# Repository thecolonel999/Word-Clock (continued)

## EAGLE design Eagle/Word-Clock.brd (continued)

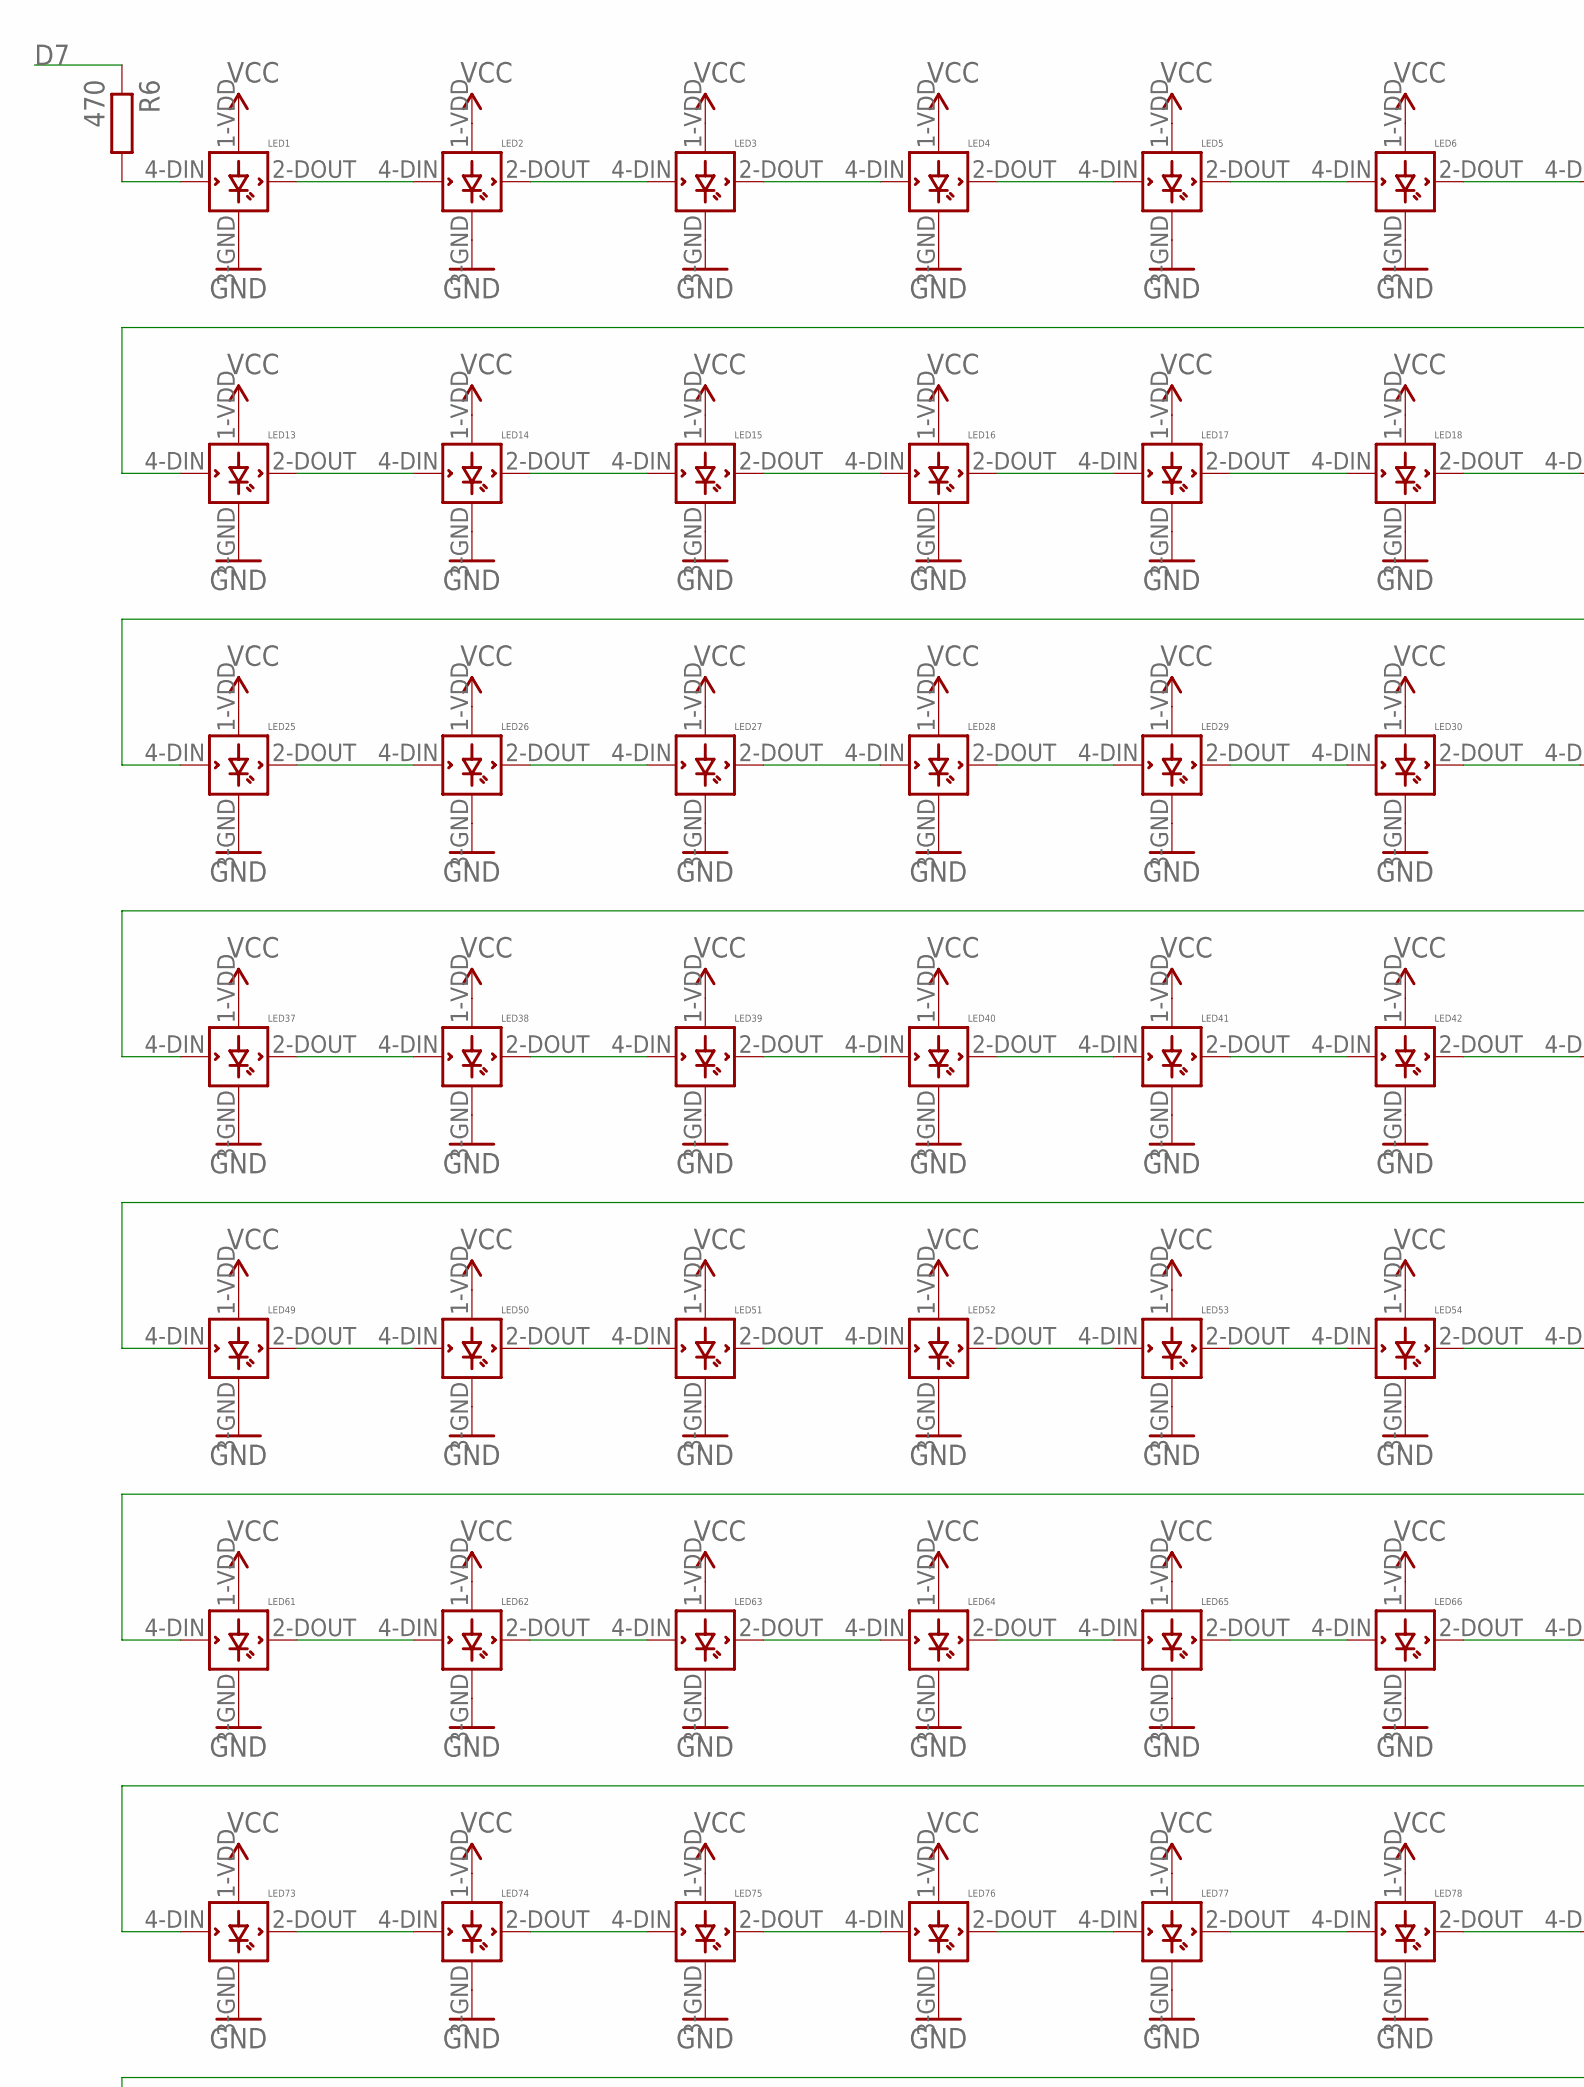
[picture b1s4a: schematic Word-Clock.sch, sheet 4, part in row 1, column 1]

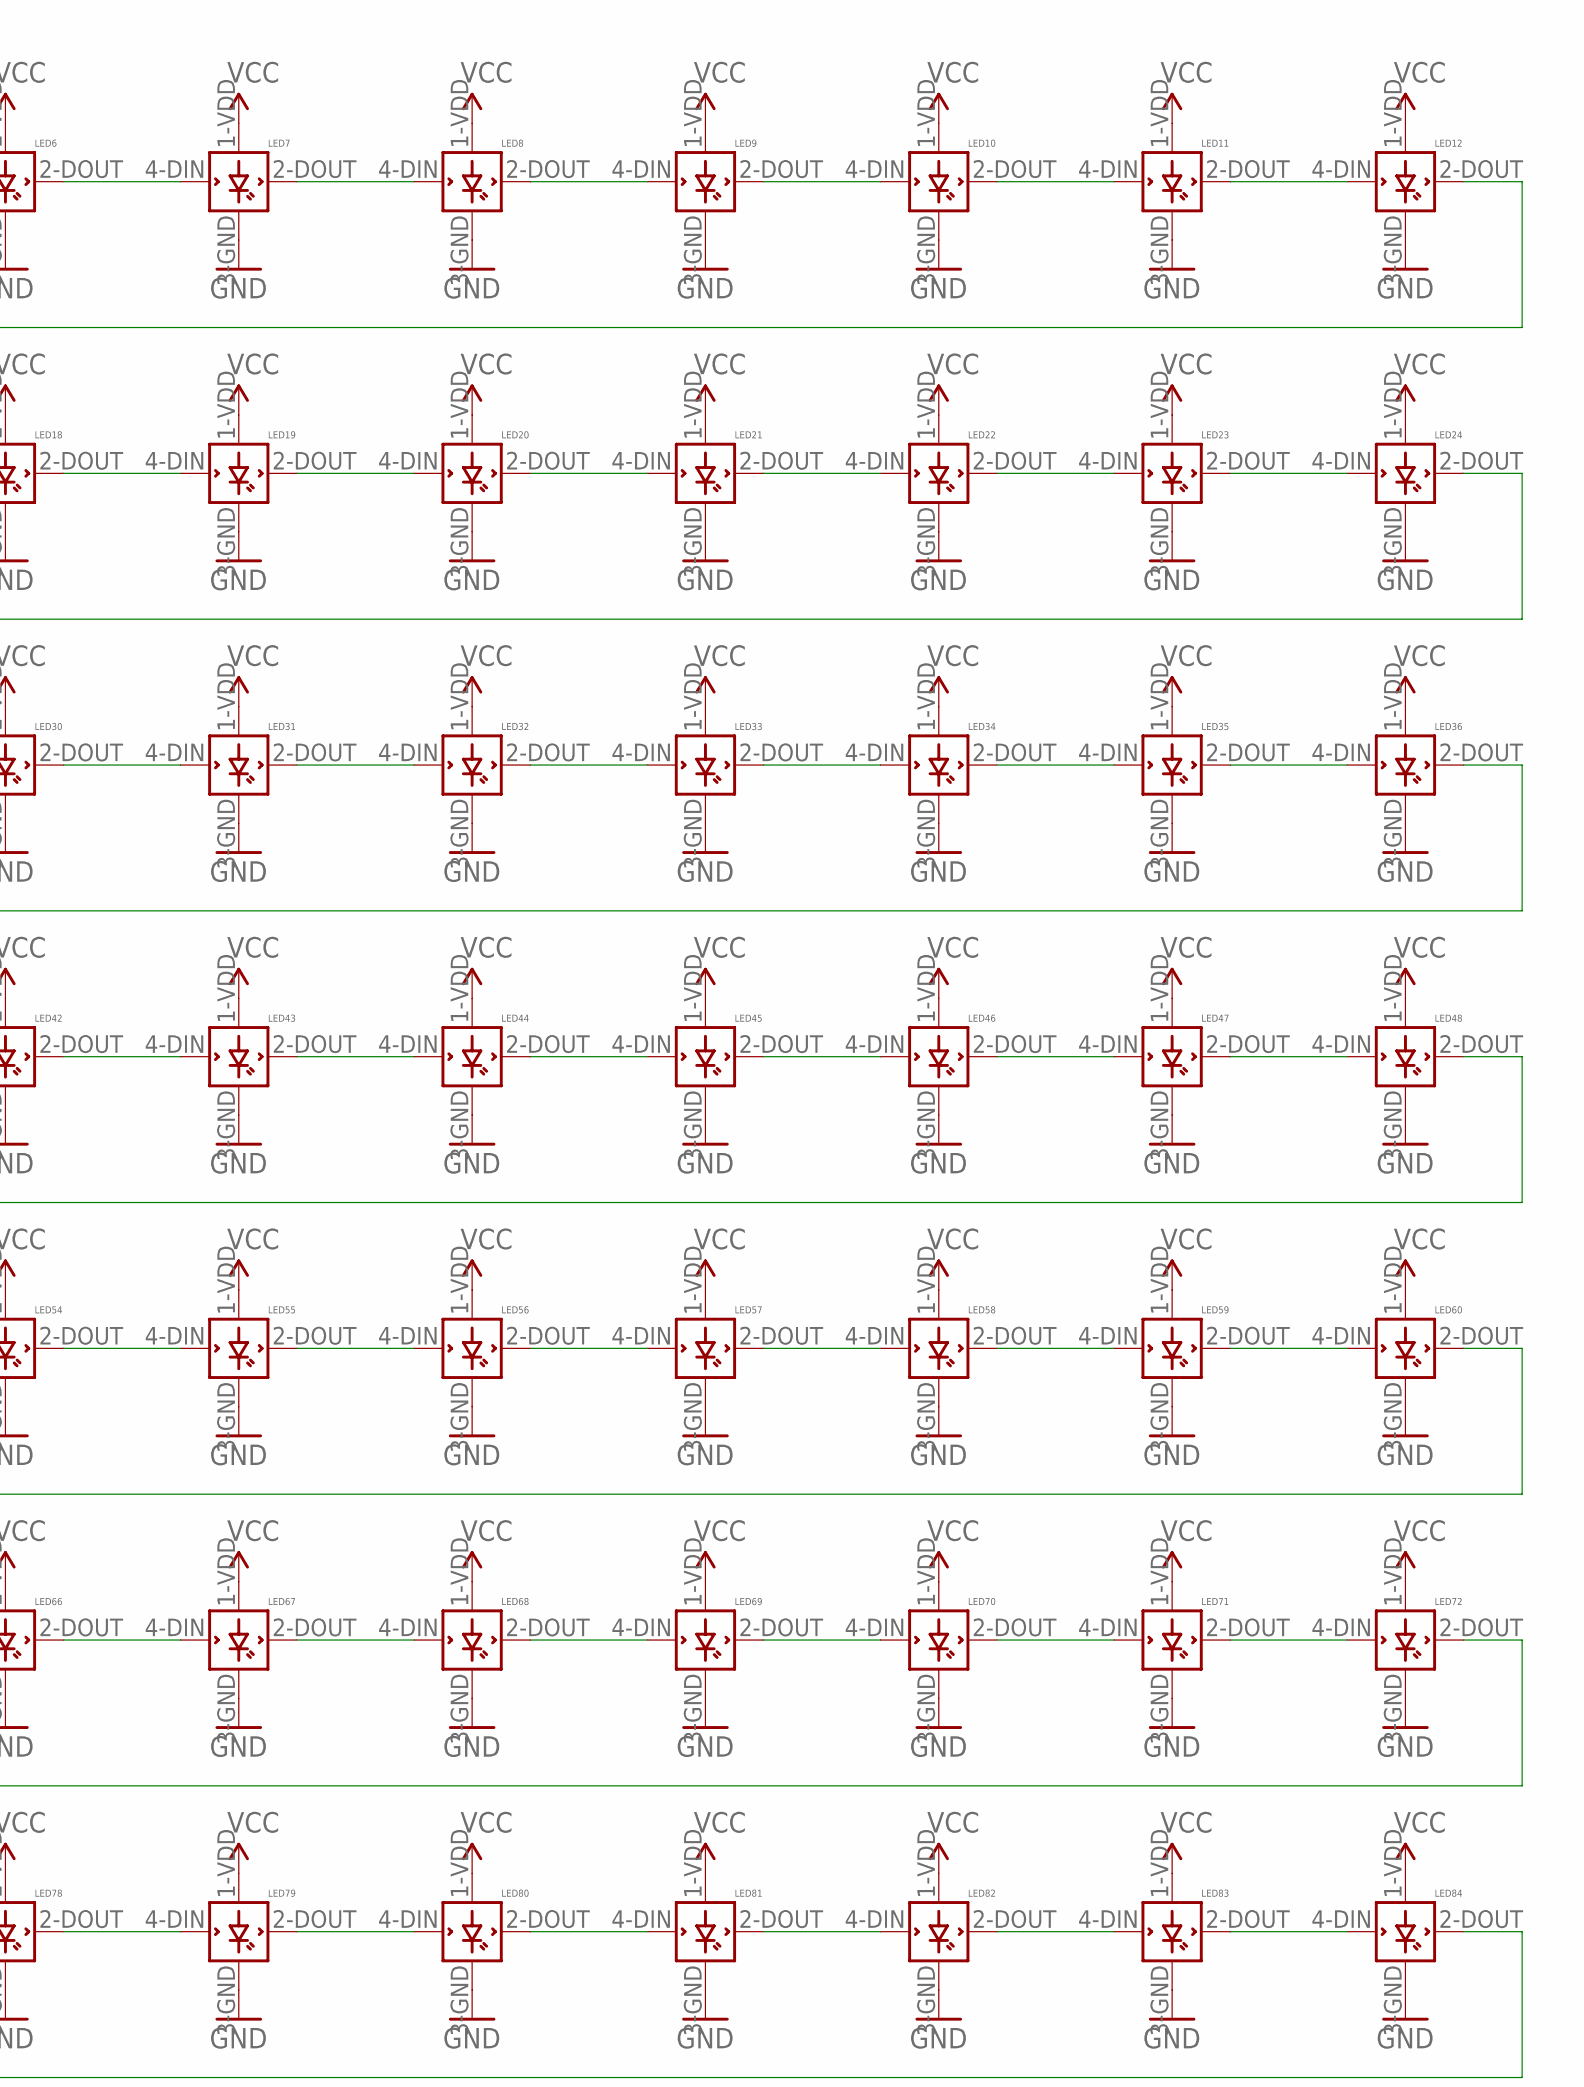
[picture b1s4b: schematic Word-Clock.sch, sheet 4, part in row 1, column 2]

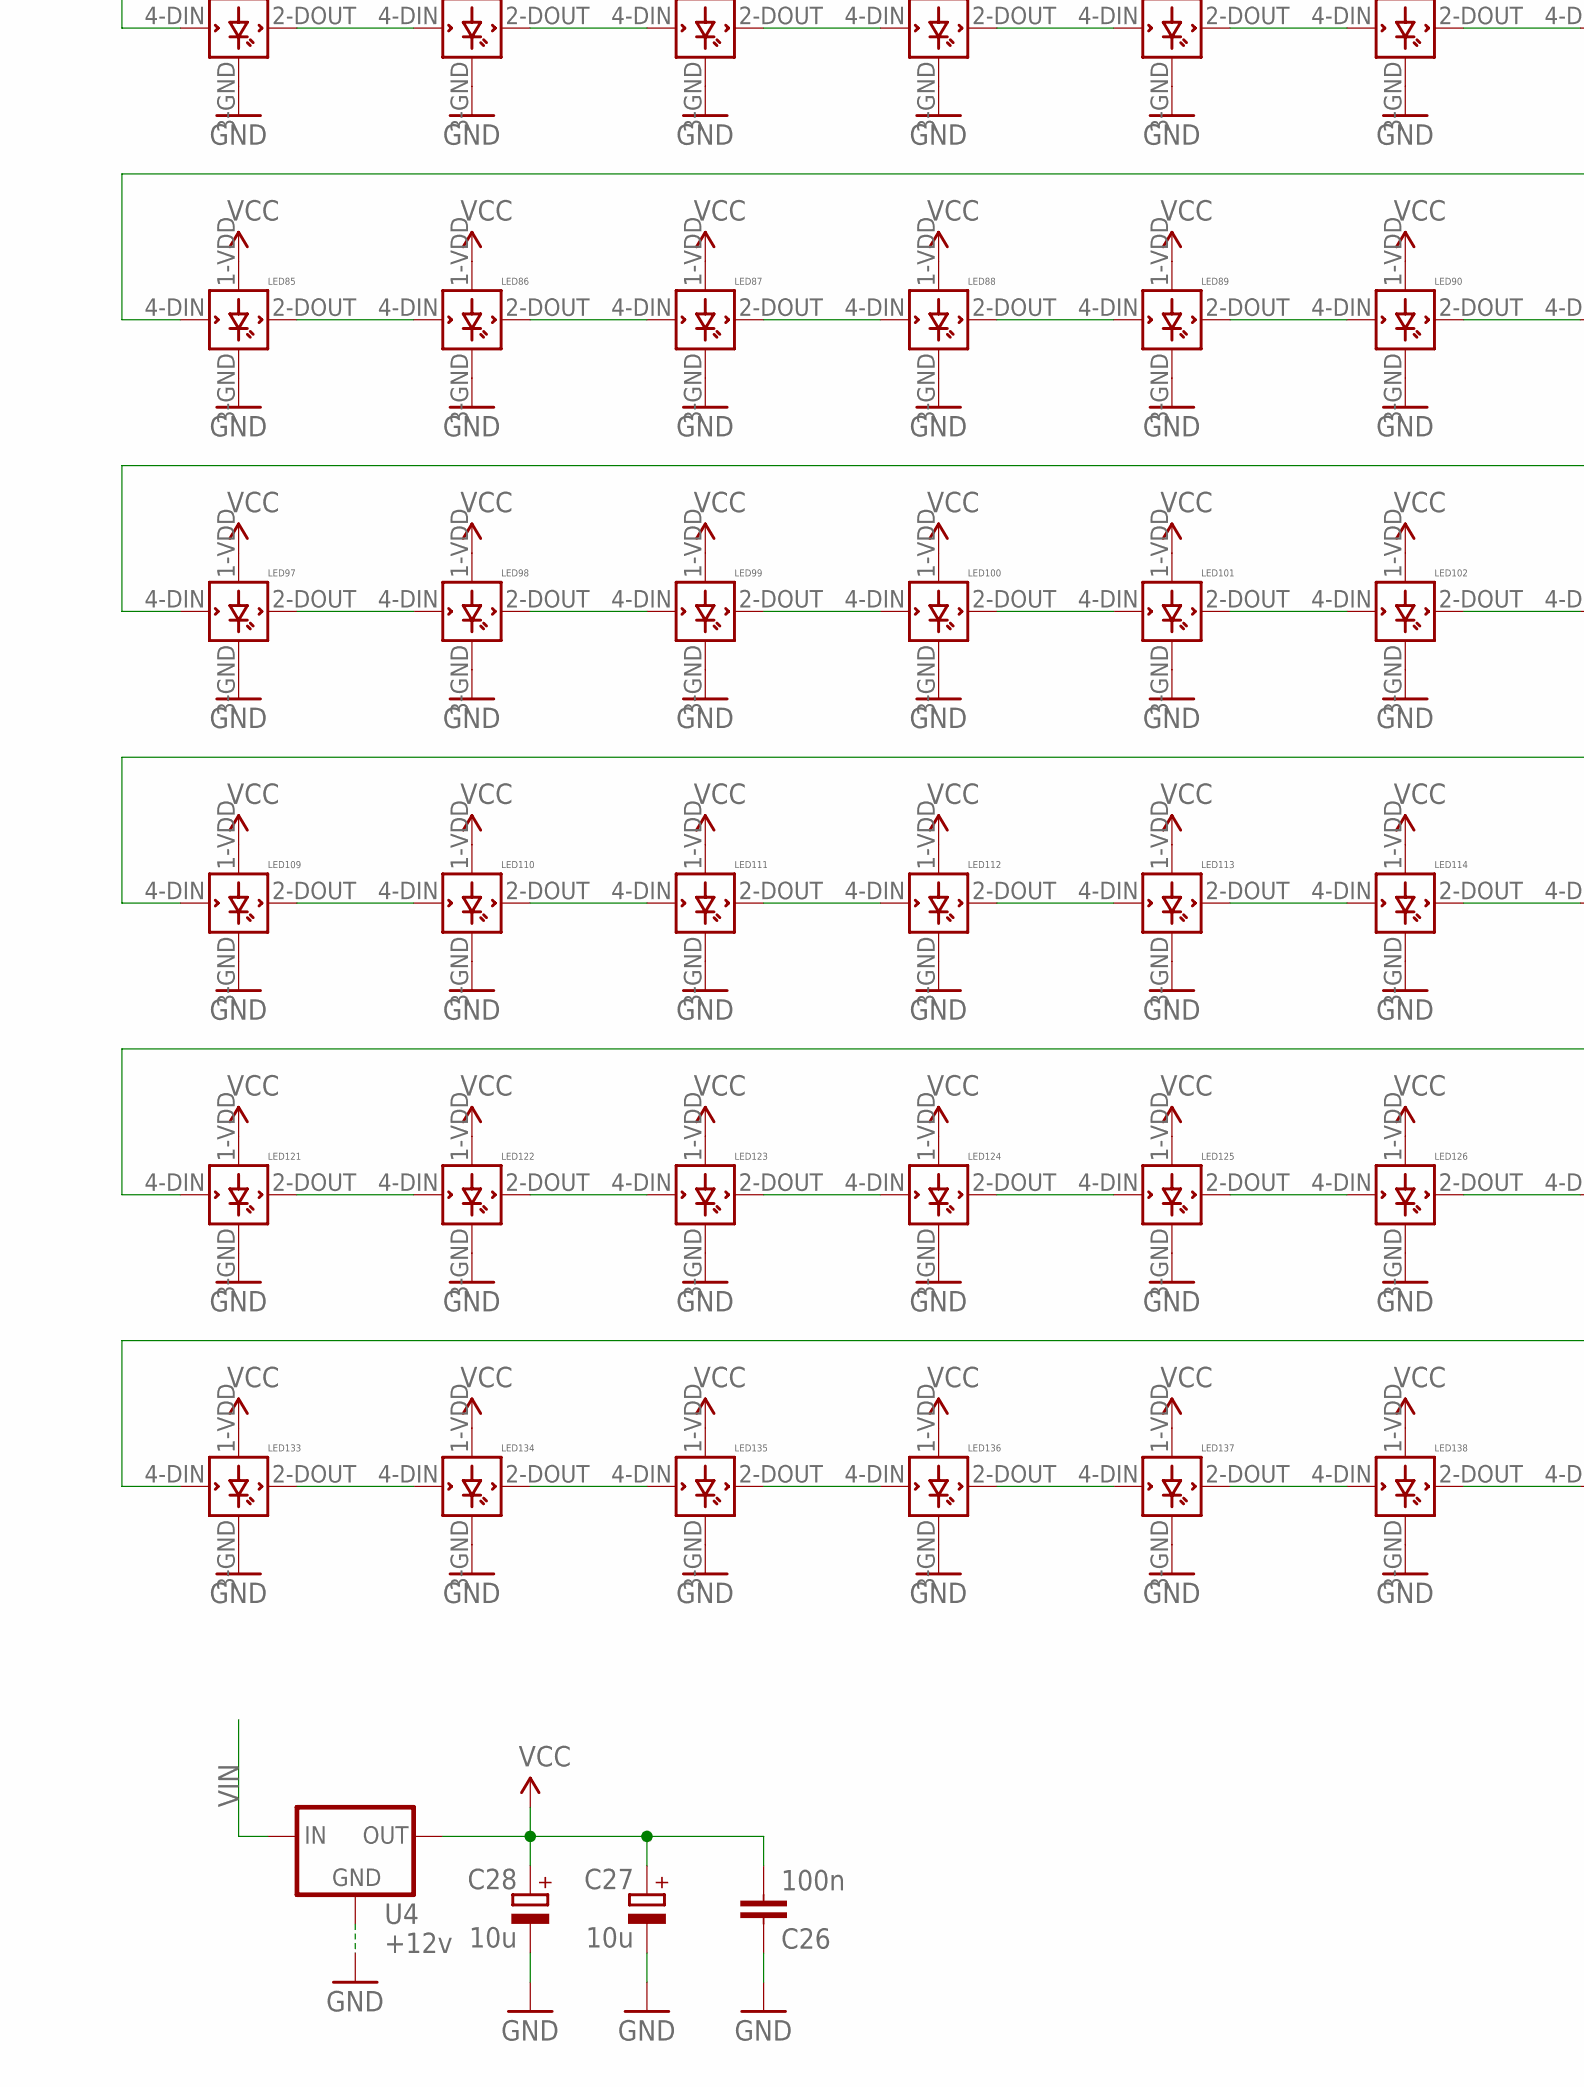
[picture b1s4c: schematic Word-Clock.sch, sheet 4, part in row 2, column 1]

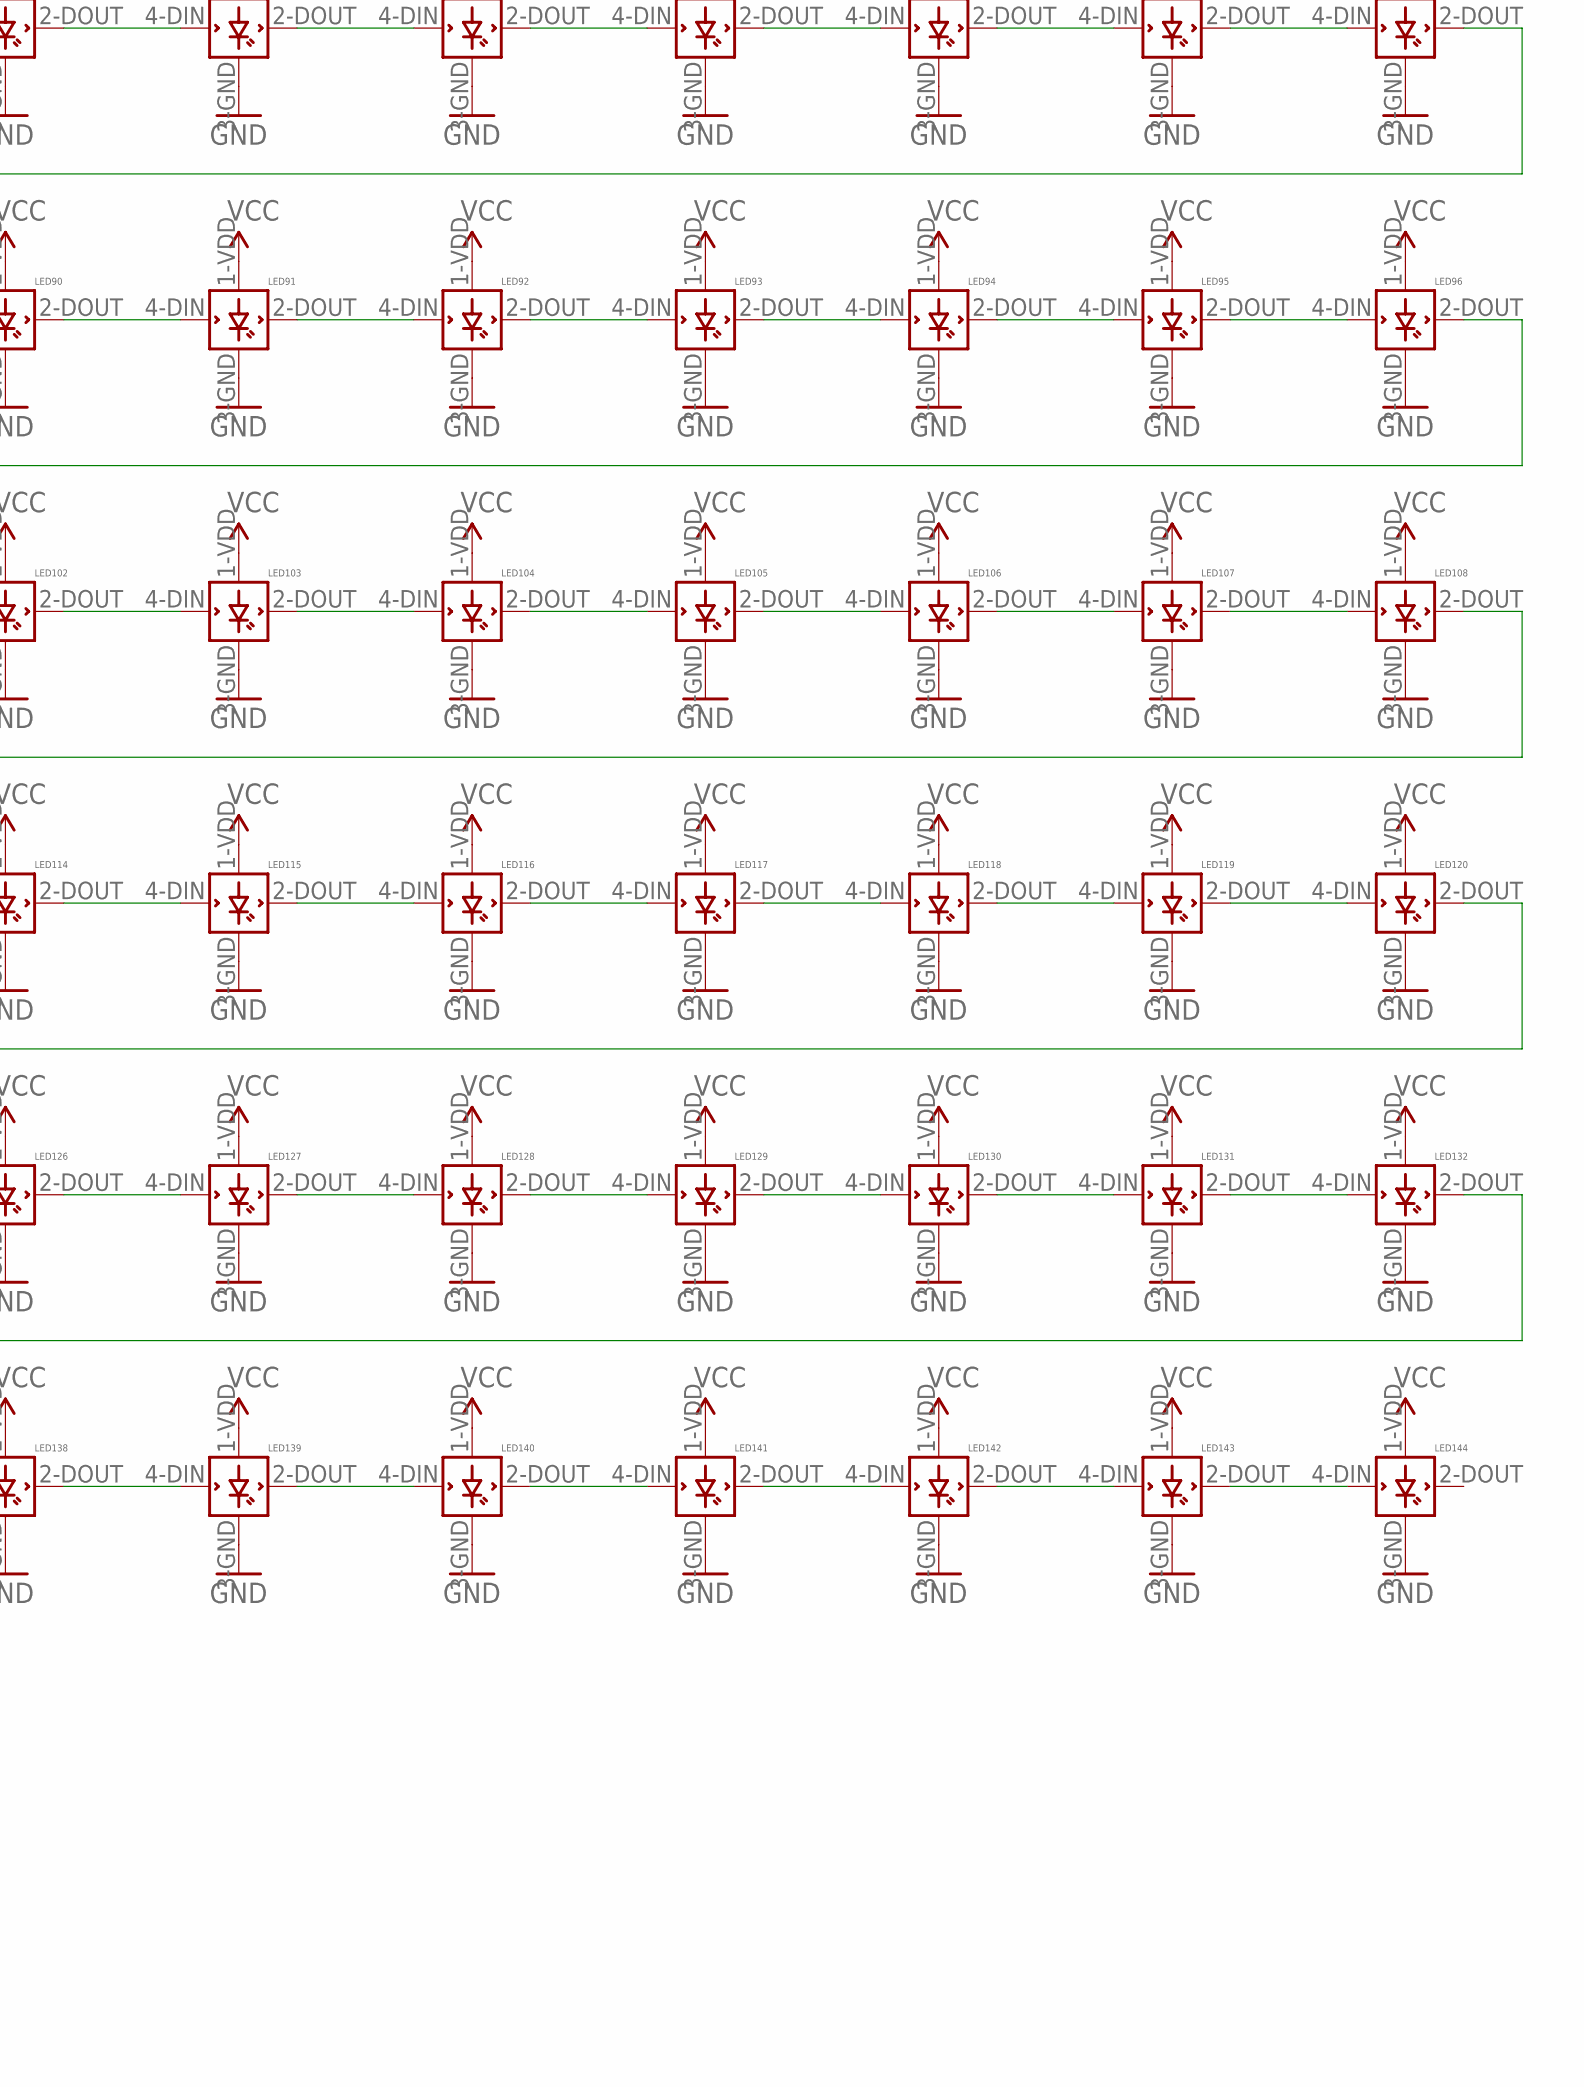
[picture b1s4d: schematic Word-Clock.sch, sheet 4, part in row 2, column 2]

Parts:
C26: 100n; C1206
C27, C28: 10u; B/3528-21W
LED1, LED2, LED3, LED4, LED5, LED6, LED7, LED8, LED9, LED10, LED11, LED12, LED13, LED14, LED15, LED16, LED17, LED18, LED19, LED20, LED21, LED22, LED23, LED24, LED25, LED26, LED27, LED28, LED29, LED30, LED31, LED32, LED33, LED34, LED35, LED36, LED37, LED38, LED39, LED40, LED41, LED42, LED43, LED44, LED45, LED46, LED47, LED48, LED49, LED50, LED51, LED52, LED53, LED54, LED55, LED56, LED57, LED58, LED59, LED60, LED61, LED62, LED63, LED64, LED65, LED66, LED67, LED68, LED69, LED70, LED71, LED72, LED73, LED74, LED75, LED76, LED77, LED78, LED79, LED80, LED81, LED82, LED83, LED84, LED85, LED86, LED87, LED88, LED89, LED90, LED91, LED92, LED93, LED94, LED95, LED96, LED97, LED98, LED99, LED100, LED101, LED102, LED103, LED104, LED105, LED106, LED107, LED108, LED109, LED110, LED111, LED112, LED113, LED114, LED115, LED116, LED117, LED118, LED119, LED120, LED121, LED122, LED123, LED124, LED125, LED126, LED127, LED128, LED129, LED130, LED131, LED132, LED133, LED134, LED135, LED136, LED137, LED138, LED139, LED140, LED141, LED142, LED143, LED144: WS2812B
R6: 470; R1206
U4: +12v; TO-252

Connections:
D7: R6.1; also elsewhere on the board
GND: C26.1, C27.-, C28.-, LED1.3-GND (GND), LED2.3-GND (GND), LED3.3-GND (GND), LED4.3-GND (GND), LED5.3-GND (GND), LED6.3-GND (GND), LED7.3-GND (GND), LED8.3-GND (GND), LED9.3-GND (GND), LED10.3-GND (GND), LED11.3-GND (GND), LED12.3-GND (GND), LED13.3-GND (GND), LED14.3-GND (GND), LED15.3-GND (GND), LED16.3-GND (GND), LED17.3-GND (GND), LED18.3-GND (GND), LED19.3-GND (GND), LED20.3-GND (GND), LED21.3-GND (GND), LED22.3-GND (GND), LED23.3-GND (GND), LED24.3-GND (GND), LED25.3-GND (GND), LED26.3-GND (GND), LED27.3-GND (GND), LED28.3-GND (GND), LED29.3-GND (GND), LED30.3-GND (GND), LED31.3-GND (GND), LED32.3-GND (GND), LED33.3-GND (GND), LED34.3-GND (GND), LED35.3-GND (GND), LED36.3-GND (GND), LED37.3-GND (GND), LED38.3-GND (GND), LED39.3-GND (GND), LED40.3-GND (GND), LED41.3-GND (GND), LED42.3-GND (GND), LED43.3-GND (GND), LED44.3-GND (GND), LED45.3-GND (GND), LED46.3-GND (GND), LED47.3-GND (GND), LED48.3-GND (GND), LED49.3-GND (GND), LED50.3-GND (GND), LED51.3-GND (GND), LED52.3-GND (GND), LED53.3-GND (GND), LED54.3-GND (GND), LED55.3-GND (GND), LED56.3-GND (GND), LED57.3-GND (GND), LED58.3-GND (GND), LED59.3-GND (GND), LED60.3-GND (GND), LED61.3-GND (GND), LED62.3-GND (GND), LED63.3-GND (GND), LED64.3-GND (GND), LED65.3-GND (GND), LED66.3-GND (GND), LED67.3-GND (GND), LED68.3-GND (GND), LED69.3-GND (GND), LED70.3-GND (GND), LED71.3-GND (GND), LED72.3-GND (GND), LED73.3-GND (GND), LED74.3-GND (GND), LED75.3-GND (GND), LED76.3-GND (GND), LED77.3-GND (GND), LED78.3-GND (GND), LED79.3-GND (GND), LED80.3-GND (GND), LED81.3-GND (GND), LED82.3-GND (GND), LED83.3-GND (GND), LED84.3-GND (GND), LED85.3-GND (GND), LED86.3-GND (GND), LED87.3-GND (GND), LED88.3-GND (GND), LED89.3-GND (GND), LED90.3-GND (GND), LED91.3-GND (GND), LED92.3-GND (GND), LED93.3-GND (GND), LED94.3-GND (GND), LED95.3-GND (GND), LED96.3-GND (GND), LED97.3-GND (GND), LED98.3-GND (GND), LED99.3-GND (GND), LED100.3-GND (GND), LED101.3-GND (GND), LED102.3-GND (GND), LED103.3-GND (GND), LED104.3-GND (GND), LED105.3-GND (GND), LED106.3-GND (GND), LED107.3-GND (GND), LED108.3-GND (GND), LED109.3-GND (GND), LED110.3-GND (GND), LED111.3-GND (GND), LED112.3-GND (GND), LED113.3-GND (GND), LED114.3-GND (GND), LED115.3-GND (GND), LED116.3-GND (GND), LED117.3-GND (GND), LED118.3-GND (GND), LED119.3-GND (GND), LED120.3-GND (GND), LED121.3-GND (GND), LED122.3-GND (GND), LED123.3-GND (GND), LED124.3-GND (GND), LED125.3-GND (GND), LED126.3-GND (GND), LED127.3-GND (GND), LED128.3-GND (GND), LED129.3-GND (GND), LED130.3-GND (GND), LED131.3-GND (GND), LED132.3-GND (GND), LED133.3-GND (GND), LED134.3-GND (GND), LED135.3-GND (GND), LED136.3-GND (GND), LED137.3-GND (GND), LED138.3-GND (GND), LED139.3-GND (GND), LED140.3-GND (GND), LED141.3-GND (GND), LED142.3-GND (GND), LED143.3-GND (GND), LED144.3-GND (GND), U4.3 (GND); also elsewhere on the board
unnamed: LED1.2-DOUT (DOUT), LED2.4-DIN (DIN)
unnamed: LED2.2-DOUT (DOUT), LED3.4-DIN (DIN)
unnamed: LED3.2-DOUT (DOUT), LED4.4-DIN (DIN)
unnamed: LED4.2-DOUT (DOUT), LED5.4-DIN (DIN)
unnamed: LED5.2-DOUT (DOUT), LED6.4-DIN (DIN)
unnamed: LED6.2-DOUT (DOUT), LED7.4-DIN (DIN)
unnamed: LED7.2-DOUT (DOUT), LED8.4-DIN (DIN)
unnamed: LED8.2-DOUT (DOUT), LED9.4-DIN (DIN)
unnamed: LED9.2-DOUT (DOUT), LED10.4-DIN (DIN)
unnamed: LED10.2-DOUT (DOUT), LED11.4-DIN (DIN)
unnamed: LED11.2-DOUT (DOUT), LED12.4-DIN (DIN)
unnamed: LED13.2-DOUT (DOUT), LED14.4-DIN (DIN)
unnamed: LED14.2-DOUT (DOUT), LED15.4-DIN (DIN)
unnamed: LED15.2-DOUT (DOUT), LED16.4-DIN (DIN)
unnamed: LED16.2-DOUT (DOUT), LED17.4-DIN (DIN)
unnamed: LED17.2-DOUT (DOUT), LED18.4-DIN (DIN)
unnamed: LED18.2-DOUT (DOUT), LED19.4-DIN (DIN)
unnamed: LED19.2-DOUT (DOUT), LED20.4-DIN (DIN)
unnamed: LED20.2-DOUT (DOUT), LED21.4-DIN (DIN)
unnamed: LED21.2-DOUT (DOUT), LED22.4-DIN (DIN)
unnamed: LED22.2-DOUT (DOUT), LED23.4-DIN (DIN)
unnamed: LED23.2-DOUT (DOUT), LED24.4-DIN (DIN)
unnamed: LED25.2-DOUT (DOUT), LED26.4-DIN (DIN)
unnamed: LED26.2-DOUT (DOUT), LED27.4-DIN (DIN)
unnamed: LED27.2-DOUT (DOUT), LED28.4-DIN (DIN)
unnamed: LED28.2-DOUT (DOUT), LED29.4-DIN (DIN)
unnamed: LED29.2-DOUT (DOUT), LED30.4-DIN (DIN)
unnamed: LED30.2-DOUT (DOUT), LED31.4-DIN (DIN)
unnamed: LED31.2-DOUT (DOUT), LED32.4-DIN (DIN)
unnamed: LED32.2-DOUT (DOUT), LED33.4-DIN (DIN)
unnamed: LED33.2-DOUT (DOUT), LED34.4-DIN (DIN)
unnamed: LED34.2-DOUT (DOUT), LED35.4-DIN (DIN)
unnamed: LED35.2-DOUT (DOUT), LED36.4-DIN (DIN)
unnamed: LED37.2-DOUT (DOUT), LED38.4-DIN (DIN)
unnamed: LED38.2-DOUT (DOUT), LED39.4-DIN (DIN)
unnamed: LED39.2-DOUT (DOUT), LED40.4-DIN (DIN)
unnamed: LED40.2-DOUT (DOUT), LED41.4-DIN (DIN)
unnamed: LED41.2-DOUT (DOUT), LED42.4-DIN (DIN)
unnamed: LED42.2-DOUT (DOUT), LED43.4-DIN (DIN)
unnamed: LED43.2-DOUT (DOUT), LED44.4-DIN (DIN)
unnamed: LED44.2-DOUT (DOUT), LED45.4-DIN (DIN)
unnamed: LED45.2-DOUT (DOUT), LED46.4-DIN (DIN)
unnamed: LED46.2-DOUT (DOUT), LED47.4-DIN (DIN)
unnamed: LED47.2-DOUT (DOUT), LED48.4-DIN (DIN)
unnamed: LED49.2-DOUT (DOUT), LED50.4-DIN (DIN)
unnamed: LED50.2-DOUT (DOUT), LED51.4-DIN (DIN)
unnamed: LED51.2-DOUT (DOUT), LED52.4-DIN (DIN)
unnamed: LED52.2-DOUT (DOUT), LED53.4-DIN (DIN)
unnamed: LED53.2-DOUT (DOUT), LED54.4-DIN (DIN)
unnamed: LED54.2-DOUT (DOUT), LED55.4-DIN (DIN)
unnamed: LED55.2-DOUT (DOUT), LED56.4-DIN (DIN)
unnamed: LED56.2-DOUT (DOUT), LED57.4-DIN (DIN)
unnamed: LED57.2-DOUT (DOUT), LED58.4-DIN (DIN)
unnamed: LED58.2-DOUT (DOUT), LED59.4-DIN (DIN)
unnamed: LED59.2-DOUT (DOUT), LED60.4-DIN (DIN)
unnamed: LED61.2-DOUT (DOUT), LED62.4-DIN (DIN)
unnamed: LED62.2-DOUT (DOUT), LED63.4-DIN (DIN)
unnamed: LED63.2-DOUT (DOUT), LED64.4-DIN (DIN)
unnamed: LED64.2-DOUT (DOUT), LED65.4-DIN (DIN)
unnamed: LED65.2-DOUT (DOUT), LED66.4-DIN (DIN)
unnamed: LED66.2-DOUT (DOUT), LED67.4-DIN (DIN)
unnamed: LED67.2-DOUT (DOUT), LED68.4-DIN (DIN)
unnamed: LED68.2-DOUT (DOUT), LED69.4-DIN (DIN)
unnamed: LED69.2-DOUT (DOUT), LED70.4-DIN (DIN)
unnamed: LED70.2-DOUT (DOUT), LED71.4-DIN (DIN)
unnamed: LED71.2-DOUT (DOUT), LED72.4-DIN (DIN)
unnamed: LED73.2-DOUT (DOUT), LED74.4-DIN (DIN)
unnamed: LED74.2-DOUT (DOUT), LED75.4-DIN (DIN)
unnamed: LED75.2-DOUT (DOUT), LED76.4-DIN (DIN)
unnamed: LED76.2-DOUT (DOUT), LED77.4-DIN (DIN)
unnamed: LED77.2-DOUT (DOUT), LED78.4-DIN (DIN)
unnamed: LED78.2-DOUT (DOUT), LED79.4-DIN (DIN)
unnamed: LED79.2-DOUT (DOUT), LED80.4-DIN (DIN)
unnamed: LED80.2-DOUT (DOUT), LED81.4-DIN (DIN)
unnamed: LED81.2-DOUT (DOUT), LED82.4-DIN (DIN)
unnamed: LED82.2-DOUT (DOUT), LED83.4-DIN (DIN)
unnamed: LED83.2-DOUT (DOUT), LED84.4-DIN (DIN)
unnamed: LED85.2-DOUT (DOUT), LED86.4-DIN (DIN)
unnamed: LED86.2-DOUT (DOUT), LED87.4-DIN (DIN)
unnamed: LED87.2-DOUT (DOUT), LED88.4-DIN (DIN)
unnamed: LED88.2-DOUT (DOUT), LED89.4-DIN (DIN)
unnamed: LED89.2-DOUT (DOUT), LED90.4-DIN (DIN)
unnamed: LED90.2-DOUT (DOUT), LED91.4-DIN (DIN)
unnamed: LED91.2-DOUT (DOUT), LED92.4-DIN (DIN)
unnamed: LED92.2-DOUT (DOUT), LED93.4-DIN (DIN)
unnamed: LED93.2-DOUT (DOUT), LED94.4-DIN (DIN)
unnamed: LED94.2-DOUT (DOUT), LED95.4-DIN (DIN)
unnamed: LED95.2-DOUT (DOUT), LED96.4-DIN (DIN)
unnamed: LED97.2-DOUT (DOUT), LED98.4-DIN (DIN)
unnamed: LED98.2-DOUT (DOUT), LED99.4-DIN (DIN)
unnamed: LED99.2-DOUT (DOUT), LED100.4-DIN (DIN)
unnamed: LED100.2-DOUT (DOUT), LED101.4-DIN (DIN)
unnamed: LED101.2-DOUT (DOUT), LED102.4-DIN (DIN)
unnamed: LED102.2-DOUT (DOUT), LED103.4-DIN (DIN)
unnamed: LED103.2-DOUT (DOUT), LED104.4-DIN (DIN)
unnamed: LED104.2-DOUT (DOUT), LED105.4-DIN (DIN)
unnamed: LED105.2-DOUT (DOUT), LED106.4-DIN (DIN)
unnamed: LED106.2-DOUT (DOUT), LED107.4-DIN (DIN)
unnamed: LED107.2-DOUT (DOUT), LED108.4-DIN (DIN)
unnamed: LED109.2-DOUT (DOUT), LED110.4-DIN (DIN)
unnamed: LED110.2-DOUT (DOUT), LED111.4-DIN (DIN)
unnamed: LED111.2-DOUT (DOUT), LED112.4-DIN (DIN)
unnamed: LED112.2-DOUT (DOUT), LED113.4-DIN (DIN)
unnamed: LED113.2-DOUT (DOUT), LED114.4-DIN (DIN)
unnamed: LED114.2-DOUT (DOUT), LED115.4-DIN (DIN)
unnamed: LED115.2-DOUT (DOUT), LED116.4-DIN (DIN)
unnamed: LED116.2-DOUT (DOUT), LED117.4-DIN (DIN)
unnamed: LED117.2-DOUT (DOUT), LED118.4-DIN (DIN)
unnamed: LED118.2-DOUT (DOUT), LED119.4-DIN (DIN)
unnamed: LED119.2-DOUT (DOUT), LED120.4-DIN (DIN)
unnamed: LED121.2-DOUT (DOUT), LED122.4-DIN (DIN)
unnamed: LED122.2-DOUT (DOUT), LED123.4-DIN (DIN)
unnamed: LED123.2-DOUT (DOUT), LED124.4-DIN (DIN)
unnamed: LED124.2-DOUT (DOUT), LED125.4-DIN (DIN)
unnamed: LED125.2-DOUT (DOUT), LED126.4-DIN (DIN)
unnamed: LED126.2-DOUT (DOUT), LED127.4-DIN (DIN)
unnamed: LED127.2-DOUT (DOUT), LED128.4-DIN (DIN)
unnamed: LED128.2-DOUT (DOUT), LED129.4-DIN (DIN)
unnamed: LED129.2-DOUT (DOUT), LED130.4-DIN (DIN)
unnamed: LED130.2-DOUT (DOUT), LED131.4-DIN (DIN)
unnamed: LED131.2-DOUT (DOUT), LED132.4-DIN (DIN)
unnamed: LED133.2-DOUT (DOUT), LED134.4-DIN (DIN)
unnamed: LED134.2-DOUT (DOUT), LED135.4-DIN (DIN)
unnamed: LED135.2-DOUT (DOUT), LED136.4-DIN (DIN)
unnamed: LED136.2-DOUT (DOUT), LED137.4-DIN (DIN)
unnamed: LED137.2-DOUT (DOUT), LED138.4-DIN (DIN)
unnamed: LED138.2-DOUT (DOUT), LED139.4-DIN (DIN)
unnamed: LED139.2-DOUT (DOUT), LED140.4-DIN (DIN)
unnamed: LED140.2-DOUT (DOUT), LED141.4-DIN (DIN)
unnamed: LED141.2-DOUT (DOUT), LED142.4-DIN (DIN)
unnamed: LED142.2-DOUT (DOUT), LED143.4-DIN (DIN)
unnamed: LED143.2-DOUT (DOUT), LED144.4-DIN (DIN)
unnamed: LED12.2-DOUT (DOUT), LED13.4-DIN (DIN)
unnamed: LED24.2-DOUT (DOUT), LED25.4-DIN (DIN)
unnamed: LED36.2-DOUT (DOUT), LED37.4-DIN (DIN)
unnamed: LED48.2-DOUT (DOUT), LED49.4-DIN (DIN)
unnamed: LED60.2-DOUT (DOUT), LED61.4-DIN (DIN)
unnamed: LED72.2-DOUT (DOUT), LED73.4-DIN (DIN)
unnamed: LED84.2-DOUT (DOUT), LED85.4-DIN (DIN)
unnamed: LED96.2-DOUT (DOUT), LED97.4-DIN (DIN)
unnamed: LED108.2-DOUT (DOUT), LED109.4-DIN (DIN)
unnamed: LED120.2-DOUT (DOUT), LED121.4-DIN (DIN)
unnamed: LED132.2-DOUT (DOUT), LED133.4-DIN (DIN)
unnamed: LED1.4-DIN (DIN), R6.2
VCC: C26.2, C27.+, C28.+, LED1.1-VDD (VDD), LED2.1-VDD (VDD), LED3.1-VDD (VDD), LED4.1-VDD (VDD), LED5.1-VDD (VDD), LED6.1-VDD (VDD), LED7.1-VDD (VDD), LED8.1-VDD (VDD), LED9.1-VDD (VDD), LED10.1-VDD (VDD), LED11.1-VDD (VDD), LED12.1-VDD (VDD), LED13.1-VDD (VDD), LED14.1-VDD (VDD), LED15.1-VDD (VDD), LED16.1-VDD (VDD), LED17.1-VDD (VDD), LED18.1-VDD (VDD), LED19.1-VDD (VDD), LED20.1-VDD (VDD), LED21.1-VDD (VDD), LED22.1-VDD (VDD), LED23.1-VDD (VDD), LED24.1-VDD (VDD), LED25.1-VDD (VDD), LED26.1-VDD (VDD), LED27.1-VDD (VDD), LED28.1-VDD (VDD), LED29.1-VDD (VDD), LED30.1-VDD (VDD), LED31.1-VDD (VDD), LED32.1-VDD (VDD), LED33.1-VDD (VDD), LED34.1-VDD (VDD), LED35.1-VDD (VDD), LED36.1-VDD (VDD), LED37.1-VDD (VDD), LED38.1-VDD (VDD), LED39.1-VDD (VDD), LED40.1-VDD (VDD), LED41.1-VDD (VDD), LED42.1-VDD (VDD), LED43.1-VDD (VDD), LED44.1-VDD (VDD), LED45.1-VDD (VDD), LED46.1-VDD (VDD), LED47.1-VDD (VDD), LED48.1-VDD (VDD), LED49.1-VDD (VDD), LED50.1-VDD (VDD), LED51.1-VDD (VDD), LED52.1-VDD (VDD), LED53.1-VDD (VDD), LED54.1-VDD (VDD), LED55.1-VDD (VDD), LED56.1-VDD (VDD), LED57.1-VDD (VDD), LED58.1-VDD (VDD), LED59.1-VDD (VDD), LED60.1-VDD (VDD), LED61.1-VDD (VDD), LED62.1-VDD (VDD), LED63.1-VDD (VDD), LED64.1-VDD (VDD), LED65.1-VDD (VDD), LED66.1-VDD (VDD), LED67.1-VDD (VDD), LED68.1-VDD (VDD), LED69.1-VDD (VDD), LED70.1-VDD (VDD), LED71.1-VDD (VDD), LED72.1-VDD (VDD), LED73.1-VDD (VDD), LED74.1-VDD (VDD), LED75.1-VDD (VDD), LED76.1-VDD (VDD), LED77.1-VDD (VDD), LED78.1-VDD (VDD), LED79.1-VDD (VDD), LED80.1-VDD (VDD), LED81.1-VDD (VDD), LED82.1-VDD (VDD), LED83.1-VDD (VDD), LED84.1-VDD (VDD), LED85.1-VDD (VDD), LED86.1-VDD (VDD), LED87.1-VDD (VDD), LED88.1-VDD (VDD), LED89.1-VDD (VDD), LED90.1-VDD (VDD), LED91.1-VDD (VDD), LED92.1-VDD (VDD), LED93.1-VDD (VDD), LED94.1-VDD (VDD), LED95.1-VDD (VDD), LED96.1-VDD (VDD), LED97.1-VDD (VDD), LED98.1-VDD (VDD), LED99.1-VDD (VDD), LED100.1-VDD (VDD), LED101.1-VDD (VDD), LED102.1-VDD (VDD), LED103.1-VDD (VDD), LED104.1-VDD (VDD), LED105.1-VDD (VDD), LED106.1-VDD (VDD), LED107.1-VDD (VDD), LED108.1-VDD (VDD), LED109.1-VDD (VDD), LED110.1-VDD (VDD), LED111.1-VDD (VDD), LED112.1-VDD (VDD), LED113.1-VDD (VDD), LED114.1-VDD (VDD), LED115.1-VDD (VDD), LED116.1-VDD (VDD), LED117.1-VDD (VDD), LED118.1-VDD (VDD), LED119.1-VDD (VDD), LED120.1-VDD (VDD), LED121.1-VDD (VDD), LED122.1-VDD (VDD), LED123.1-VDD (VDD), LED124.1-VDD (VDD), LED125.1-VDD (VDD), LED126.1-VDD (VDD), LED127.1-VDD (VDD), LED128.1-VDD (VDD), LED129.1-VDD (VDD), LED130.1-VDD (VDD), LED131.1-VDD (VDD), LED132.1-VDD (VDD), LED133.1-VDD (VDD), LED134.1-VDD (VDD), LED135.1-VDD (VDD), LED136.1-VDD (VDD), LED137.1-VDD (VDD), LED138.1-VDD (VDD), LED139.1-VDD (VDD), LED140.1-VDD (VDD), LED141.1-VDD (VDD), LED142.1-VDD (VDD), LED143.1-VDD (VDD), LED144.1-VDD (VDD), U4.2 (OUT)
VIN: U4.1 (IN); also elsewhere on the board
